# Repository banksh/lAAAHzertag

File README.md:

lAAAHzertag
===========

Microphone-triggered laser tag game

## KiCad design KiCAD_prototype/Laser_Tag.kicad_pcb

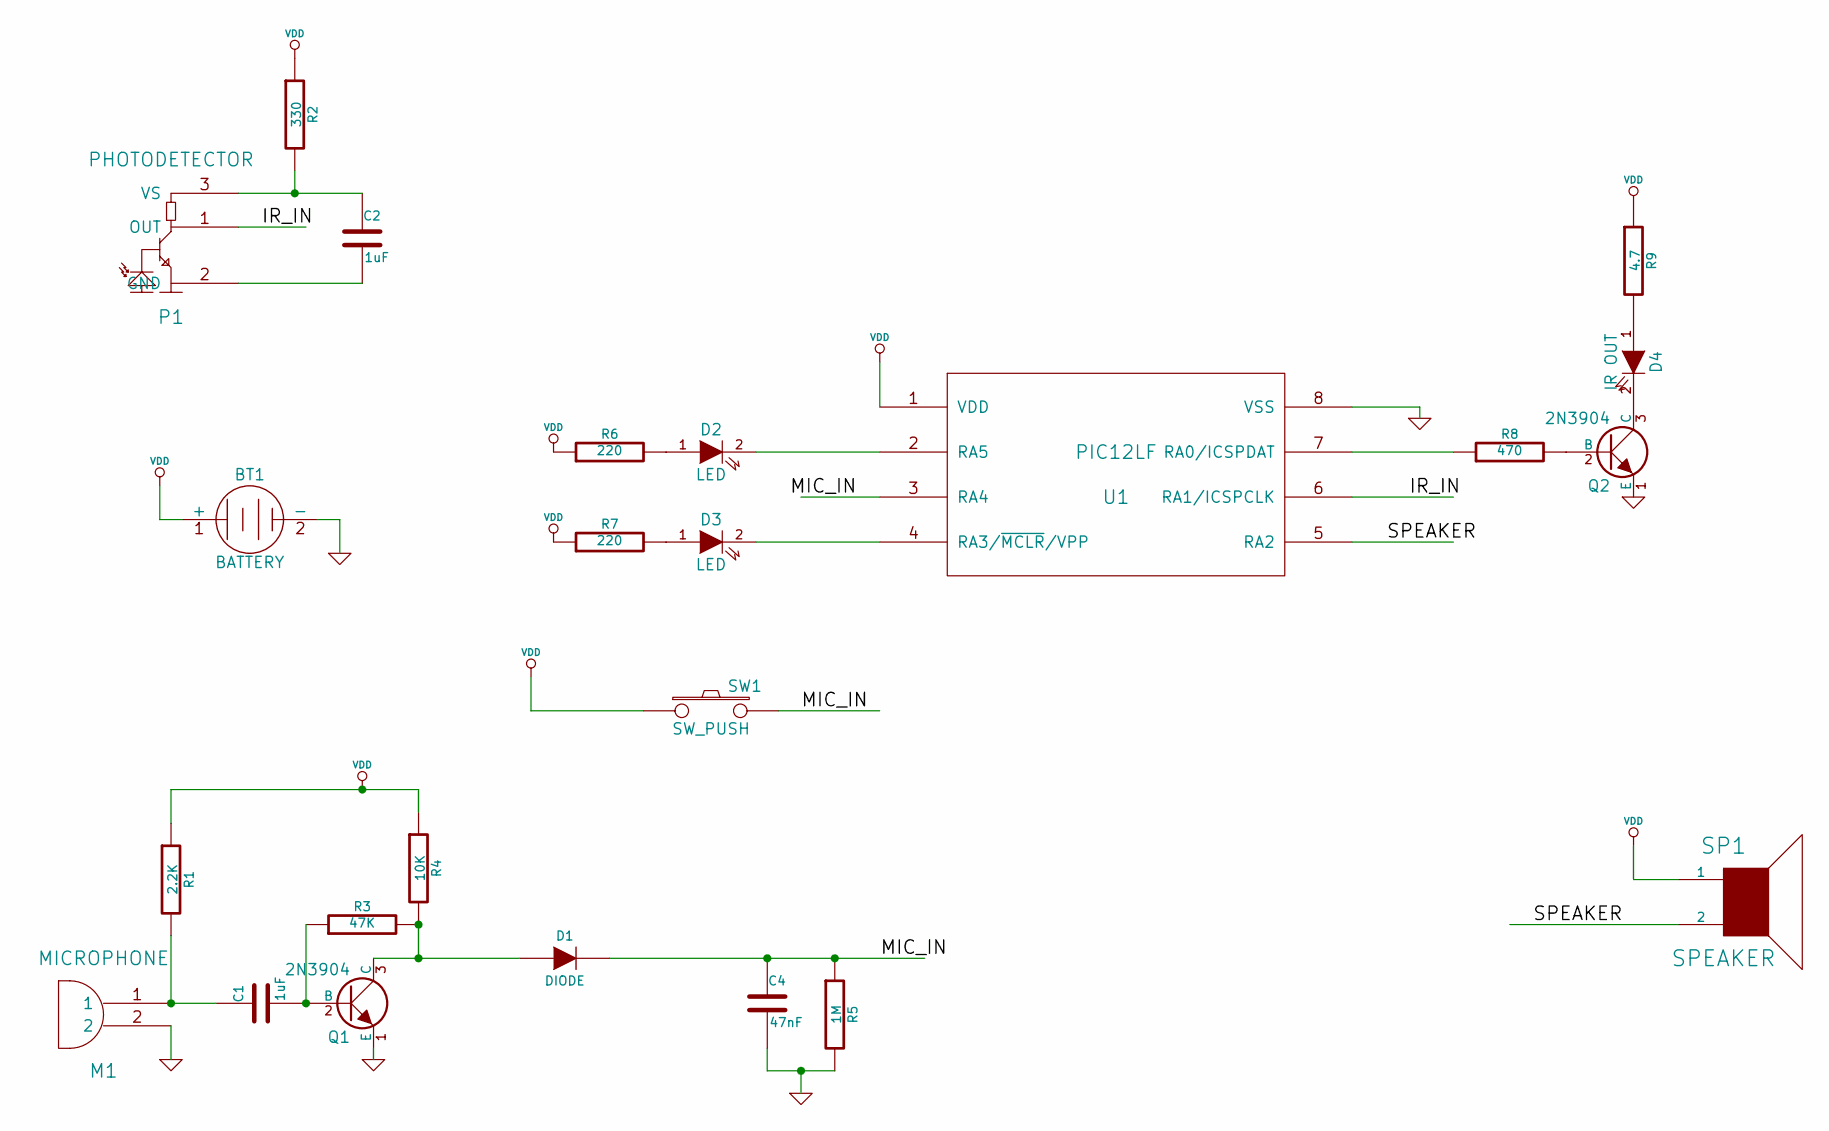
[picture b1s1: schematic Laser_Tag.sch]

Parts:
BT1: BATTERY
C1, C2: 1uF
C4: 47nF
D1: DIODE
D2, D3: LED
D4: IR OUT
M1: MICROPHONE
P1: PHOTODETECTOR
Q1, Q2: 2N3904
R1: 2.2K
R2: 330
R3: 47K
R4: 10K
R5: 1M
R6, R7: 220
R8: 470
R9: 4.7
SP1: SPEAKER
SW1: SW_PUSH
U1: PIC12LF

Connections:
/IR_IN: P1.1 (OUT), U1.6 (RA1/ICSPCLK)
/MIC_IN: C4.1, D1.2 (K), R5.1, SW1.2, U1.3 (RA4)
/SPEAKER: SP1.2, U1.5 (RA2)
GND: BT1.2 (-), C4.2, M1.2, Q1.1 (E), Q2.1 (E), R5.2, U1.8 (VSS)
unnamed: D2.1 (A), R6.2
unnamed: D3.1 (A), R7.2
unnamed: Q2.2 (B), R8.2
unnamed: C1.1, M1.1, R1.2
unnamed: C1.2, Q1.2 (B), R3.1
unnamed: D4.2 (K), Q2.3 (C)
unnamed: D4.1 (A), R9.2
unnamed: R8.1, U1.7 (RA0/ICSPDAT)
unnamed: D1.1 (A), Q1.3 (C), R3.2, R4.2
unnamed: C2.1, P1.3 (VS), R2.2
unnamed: C2.2, P1.2 (GND)
unnamed: D2.2 (K), U1.2 (RA5)
unnamed: D3.2 (K), U1.4 (RA3/~MCLR~/VPP)
VDD: BT1.1 (+), R1.1, R2.1, R4.1, R6.1, R7.1, R9.1, SP1.1, SW1.1, U1.1 (VDD)

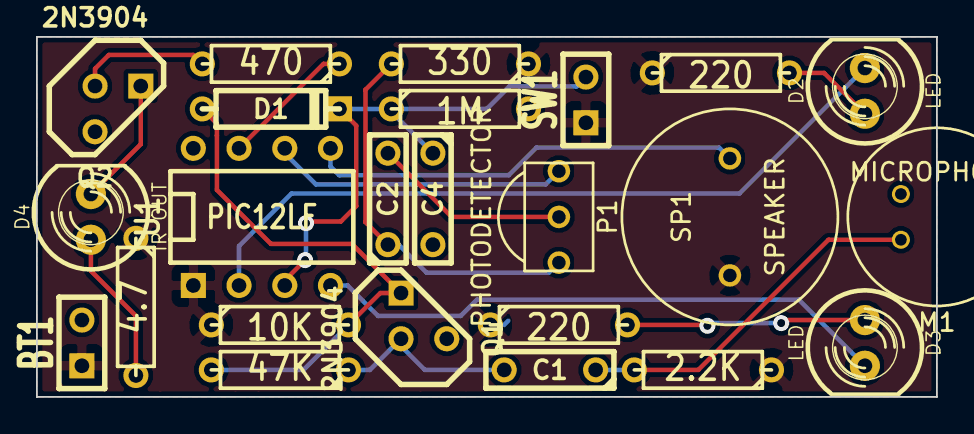
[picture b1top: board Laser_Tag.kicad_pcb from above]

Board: 2 copper layers, 50.0 x 20.0 mm, 24 parts (0 on the bottom side), 18 nets.

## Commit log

2014-07-27 Added everything
2014-07-27 Added switch
2014-07-27 Added envelope follow
2014-07-27 Finished board layout
2014-07-27 Added PCB CAD
2014-07-27 Moved stuff around
2014-07-28 Changed component values, added video
2014-07-28 First prototype version sent to PCB fab
2014-07-28 Added microchip RFP
2014-07-29 Started writing firmware
2014-07-30 HAL updates
2014-08-16 Modulated IR transmit working
2014-08-16 adding basic base station functionality
2014-08-16 Fleshed out more commands and added stubs for a database to store logs
2014-08-16 adding some C support for communication
2014-08-17 Adding base station PIC10F200 code
2014-08-17 Base station to gun protocol working
2014-08-17 fixing up some base station stuff
2014-08-17 adding pretend gun
2014-08-17 Flash memory read/erase/write
2014-08-17 Save/load working correctly
2014-08-18 Comms working, registers hits, etc
2014-08-19 my laser gun it goes pew pew
2014-08-19 implemented getting hit death sequence
2014-08-20 Boop boop
2014-08-20 why am i even committing this code it is so terrible
2014-08-21 base station is a little bit nicer now
2014-08-21 no more cheating
2014-08-22 Created database initializion script
2014-08-23 Replicated memorydb functionality
2014-08-23 adding graphics
2014-08-23 adding XOR improvement
2014-08-23 Firmware finalized
2014-08-24 Added blacklist
2014-08-24 Added config and hits
2014-08-24 cad files
2014-08-24 added web interface, sorta
2014-08-24 Rearrange web app for flask
2014-08-24 Adding .* and vim swapfiles to gitignore
2014-08-24 dependencies for web
2014-08-24 Fixing @maxjusticz 's db code
2014-08-24 Basic high score lists
2014-08-24 working ish maybe
2014-08-24 Forgot gun.html
2014-08-24 base station working too?
2014-08-24 HTML
2014-08-24 removed the weird ID initialized state, i think it works better this way but i haven't really slept
2014-08-24 re-added some config initialization
2014-08-25 Took out unnecessary initialization
    Firmware now actually builds successfully
2014-08-25 Wrote instructions page
2014-08-25 nothing of substance
2014-08-25 Fixing some styling
2014-08-25 Added gun images
2014-08-25 Fixing Most Hit & css
2014-08-25 SQL joins; html tweaks
2014-08-25 Write config & admin.py
2014-08-25 Changes to instructions
2014-08-25 Fixed tabs
2014-08-25 more db commands
2014-08-25 Fixing @zbanks's dumb mistakes
2014-08-26 lazzors
2014-08-27 Don't make this mistake
